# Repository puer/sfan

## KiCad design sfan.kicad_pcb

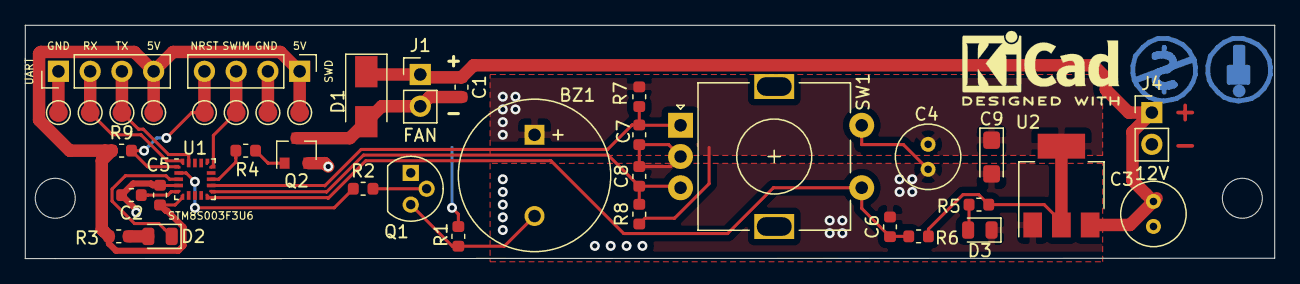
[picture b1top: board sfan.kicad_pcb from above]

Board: 2 copper layers, 100.0 x 18.7 mm, 39 parts (0 on the bottom side), 20 nets.

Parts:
BZ1: Buzzer; MagneticBuzzer_ProSignal_ABT-410-RC
C1, C5, C6, C7, C8: 104; C_0603_1608Metric
C2: 474; C_0603_1608Metric
C3, C4: 100u; C_Radial_D5.0mm_H7.0mm_P2.00mm
C9: 22u; CP_EIA-3216-10_Kemet-I
D1: D; D_SMA
D2, D3: LED; LED_0805_2012Metric
J1: FAN; PinHeader_1x02_P2.54mm_Vertical
J4: 12V; PinHeader_1x02_P2.54mm_Vertical
Q1: Q_NPN_EBC; TO-92
Q2: SI2300; SOT-23
R1: 1K; C_0603_1608Metric
R2, R4: 100; C_0603_1608Metric
R3, R5: 2K; C_0603_1608Metric
R6, R7, R8, R9: 103; R_0603_1608Metric
SW1: Rotary_Encoder_Switch; RotaryEncoder_Alps_EC11E-Switch_Vertical_H20mm
SWD: SWIM; PinHeader_1x04_P2.54mm_Vertical
TP1: RX; TestPoint_Pad_D1.5mm
TP2: NRST; TestPoint_Pad_D1.5mm
TP3: TX; TestPoint_Pad_D1.5mm
TP4, TP5: GND; TestPoint_Pad_D1.5mm
TP6: SWIM; TestPoint_Pad_D1.5mm
TP7, TP8: 5V; TestPoint_Pad_D1.5mm
U1: STM8S003F3U; ST_UFQFPN-20_3x3mm_P0.5mm
U2: AMS1117-5.0; SOT-223-3_TabPin2
UART: UART; PinHeader_1x04_P2.54mm_Vertical

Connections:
+5V: BZ1.1, C4.1, C5.1, C9.1, R1.1, R3.1, R5.1, R6.1, R7.1, R8.1, R9.1, SWD.1, TP7.1, TP8.1, U1.6, U2.2, UART.4
/+12V: C1.1, C3.1, D1.1, J1.1, J4.1, U2.3
/BEEP: R2.1, U1.2
/PSBTN: C6.1, R6.2, SW1.S1, U1.10
/PWM: R4.1, U1.13
/REA: C7.1, R7.2, SW1.A, U1.12
/REB: C8.1, R8.2, SW1.B, U1.11
GND: C2.2, C3.2, C4.2, C5.2, C6.2, C7.2, C8.2, C9.2, D3.1, J4.2, Q1.1, Q2.2, SW1.C, SW1.S2, SWD.2, TP4.1, TP5.1, U1.4, U2.1, UART.1
unnamed: BZ1.2, Q1.3, R1.2
unnamed: C1.2, D1.2, J1.2, Q2.3
unnamed: C2.1, U1.5
unnamed: D2.1, U1.3
unnamed: D2.2, R3.2
unnamed: D3.2, R5.2
unnamed: TP1.1, U1.20, UART.2
unnamed: TP3.1, U1.19, UART.3
unnamed: SWD.3, TP6.1, U1.15
unnamed: R9.2, SWD.4, TP2.1, U1.1
unnamed: Q1.2, R2.2
unnamed: Q2.1, R4.2

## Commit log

2019-11-25 init
2019-11-29 pcb layout
2019-11-29 update refine
2019-11-29 comply to jlc's 10cm limit
2019-12-02 solder mask adj. this problem cost me 5 yuan and another round of production
2019-12-02 git ignore
2020-12-07 gitignore update
